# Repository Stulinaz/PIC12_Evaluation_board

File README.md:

# PIC12_Evaluation_board
kicad project of my custom PIC12 evaluation board

I'm Enrico and i am FCT board tester. I designed this board for rapid design of 8 pin microcontroller application that support my work.

The pic 12 board include:

-PICKIT connector on board.

-Large build area.

-Double Power supply from usb connector or from CR2032 battery for portable applications.

-Supports pullup and pulldown resistors for every pin.

-BOM is displayed on bottom silkscreen side.

TOP SIDE:

BOTTOM SIDE:

ASSEMBLED PCB:

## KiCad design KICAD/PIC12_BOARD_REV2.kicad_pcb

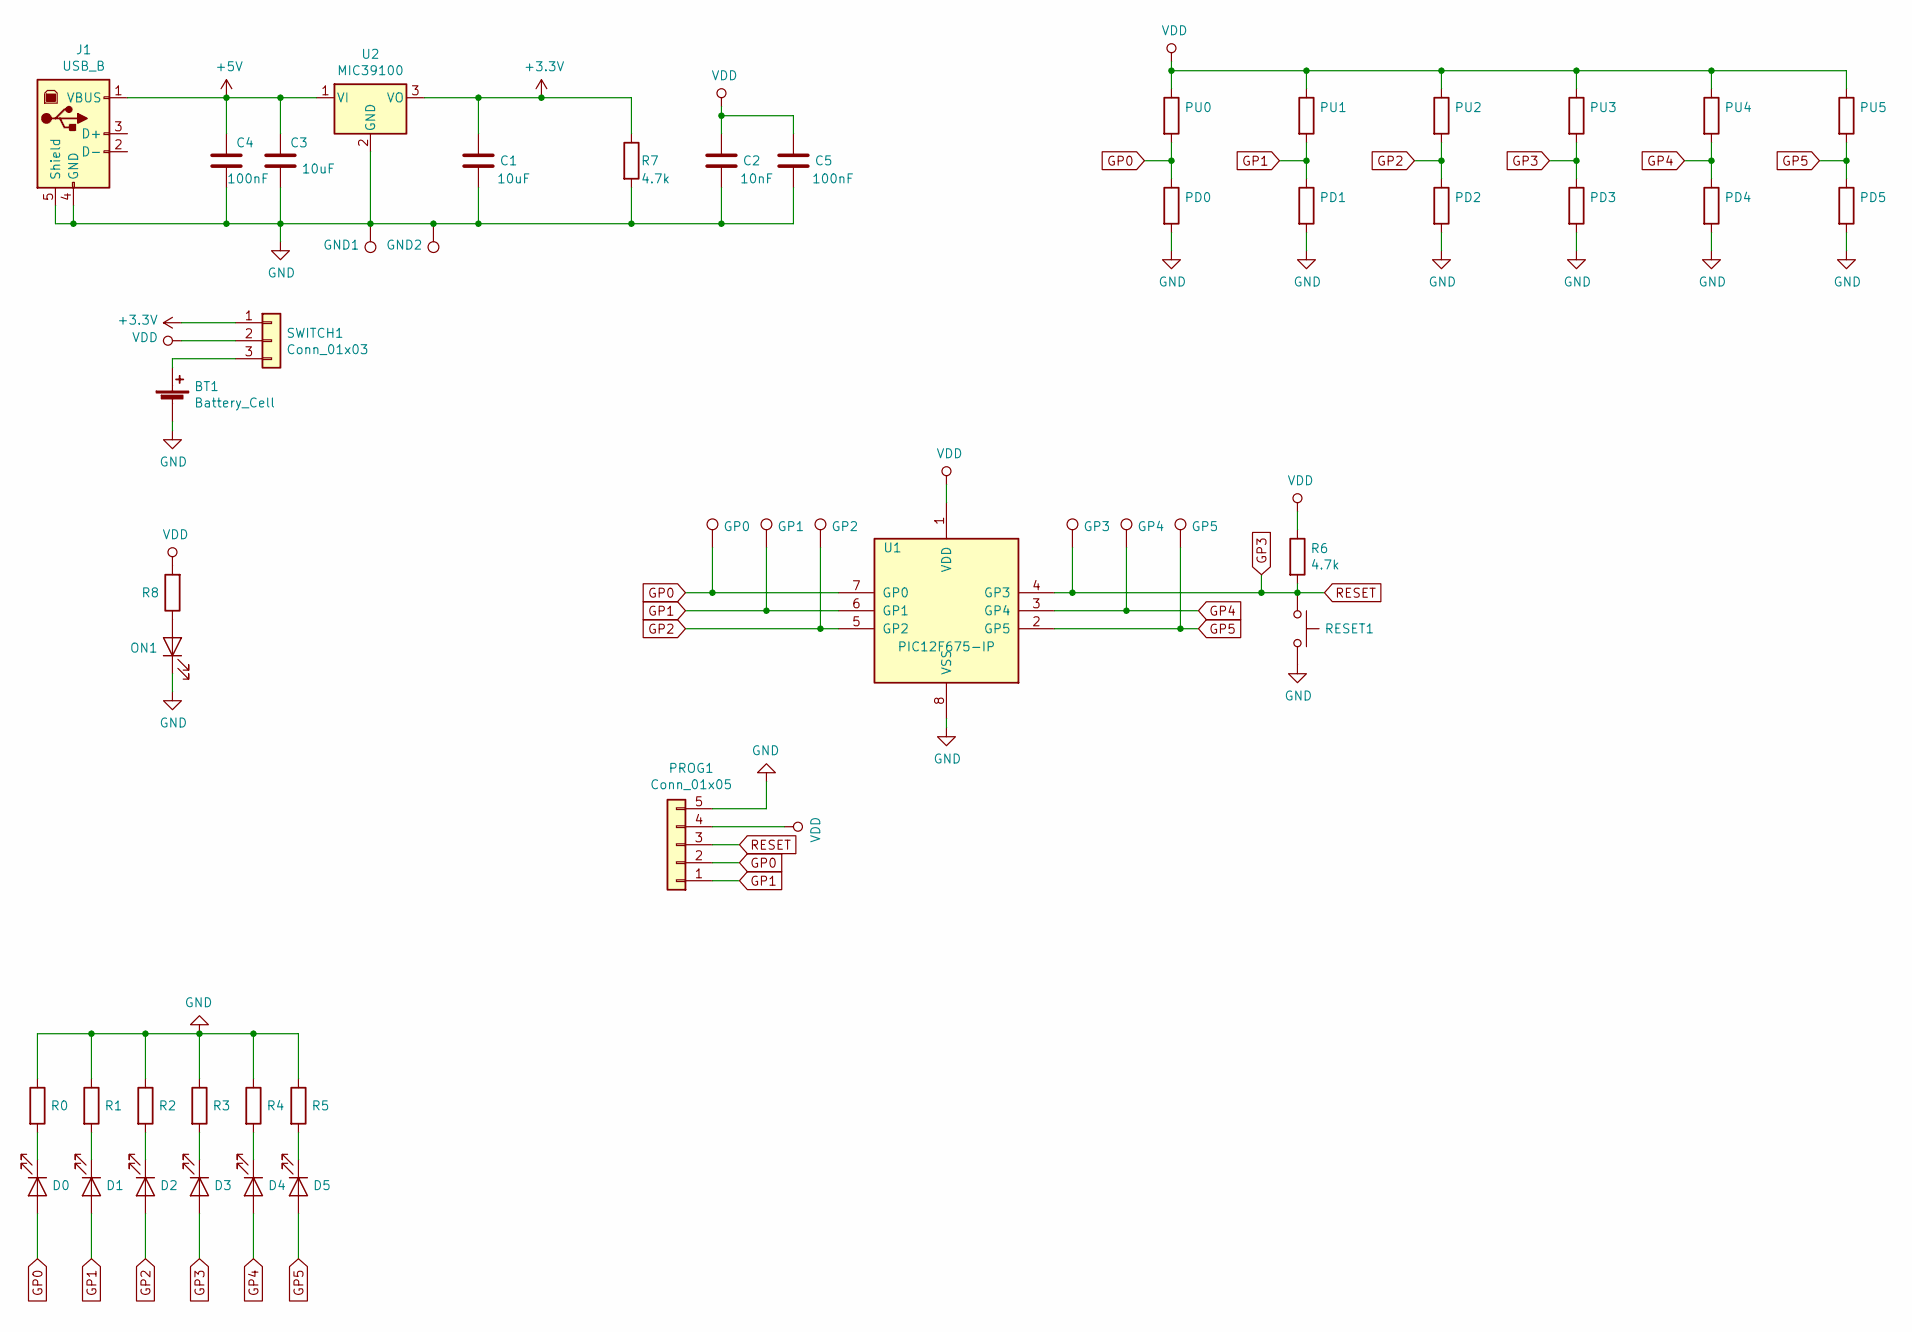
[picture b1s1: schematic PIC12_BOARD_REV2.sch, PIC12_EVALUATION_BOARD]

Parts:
BT1: Battery_Cell; BatteryHolder_Keystone_3034_1x20mm
C1, C3: 10uF; R_0805_2012Metric_Pad1.15x1.40mm_HandSolder
C2: 10nF; R_0805_2012Metric_Pad1.15x1.40mm_HandSolder
C4, C5: 100nF; R_0805_2012Metric_Pad1.15x1.40mm_HandSolder
D0, D1, D2, D3, D4, D5: LED; R_0805_2012Metric_Pad1.15x1.40mm_HandSolder
GND1, GND2: TestPoint; TP_EN0
GP0, GP1, GP2, GP3, GP4, GP5: TestPoint; TP_EN0
J1: USB_B; USB_Mini-B_Lumberg_2486_01_Horizontal
ON1: LED; R_0805_2012Metric_Pad1.15x1.40mm_HandSolder
PD0, PD1, PD2, PD3, PD4, PD5: 4.7k; R_0805_2012Metric_Pad1.15x1.40mm_HandSolder
PROG1: Conn_01x05; PinSocket_1x05_P2.54mm_Vertical
PU0, PU1, PU2, PU3, PU4, PU5: 4.7k; R_0805_2012Metric_Pad1.15x1.40mm_HandSolder
R0, R1, R2, R3, R4, R5: R; R_0805_2012Metric_Pad1.15x1.40mm_HandSolder
R6: 4.7k; R_0805_2012Metric
R7: 4.7k; R_0805_2012Metric_Pad1.15x1.40mm_HandSolder
R8: 220; R_0805_2012Metric_Pad1.15x1.40mm_HandSolder
RESET1: SW_Push; SW_PUSH_6mm
SWITCH1: Conn_01x03; PinHeader_1x03_P2.54mm_Vertical
U1: PIC12F675-IP; DIP-8_W7.62mm
U2: MIC39100; SOT-223-3_TabPin2

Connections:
+3V3: C1.1, R7.1, SWITCH1.1, U2.3 (VO)
+5V: C3.1, C4.1, J1.1 (VBUS), U2.1 (VI)
DATA+: J1.3 (D+)
DATA-: J1.2 (D-)
GND: BT1.2 (-), C1.2, C2.2, C3.2, C4.2, C5.2, GND1.1, GND2.1, J1.4 (GND), J1.5 (Shield), J1.6, ON1.1 (K), PD0.2, PD1.2, PD2.2, PD3.2, PD4.2, PD5.2, PROG1.5, R0.1, R1.1, R2.1, R3.1, R4.1, R5.1, R7.2, RESET1.2, U1.8 (VSS), U2.2 (GND)
GP0: D0.2 (A), GP0.1, PD0.1, PROG1.2, PU0.2, U1.7 (GP0)
GP1: D1.2 (A), GP1.1, PD1.1, PROG1.1, PU1.2, U1.6 (GP1)
GP2: D2.2 (A), GP2.1, PD2.1, PU2.2, U1.5 (GP2)
GP3: D3.2 (A), GP3.1, PD3.1, PROG1.3, PU3.2, R6.2, RESET1.1, U1.4 (GP3)
GP4: D4.2 (A), GP4.1, PD4.1, PU4.2, U1.3 (GP4)
GP5: D5.2 (A), GP5.1, PD5.1, PU5.2, U1.2 (GP5)
unnamed: BT1.1 (+), SWITCH1.3
unnamed: D0.1 (K), R0.2
unnamed: D1.1 (K), R1.2
unnamed: D2.1 (K), R2.2
unnamed: D3.1 (K), R3.2
unnamed: D4.1 (K), R4.2
unnamed: D5.1 (K), R5.2
unnamed: ON1.2 (A), R8.1
VDD: C2.1, C5.1, PROG1.4, PU0.1, PU1.1, PU2.1, PU3.1, PU4.1, PU5.1, R6.1, R8.2, SWITCH1.2, U1.1 (VDD); also elsewhere on the board

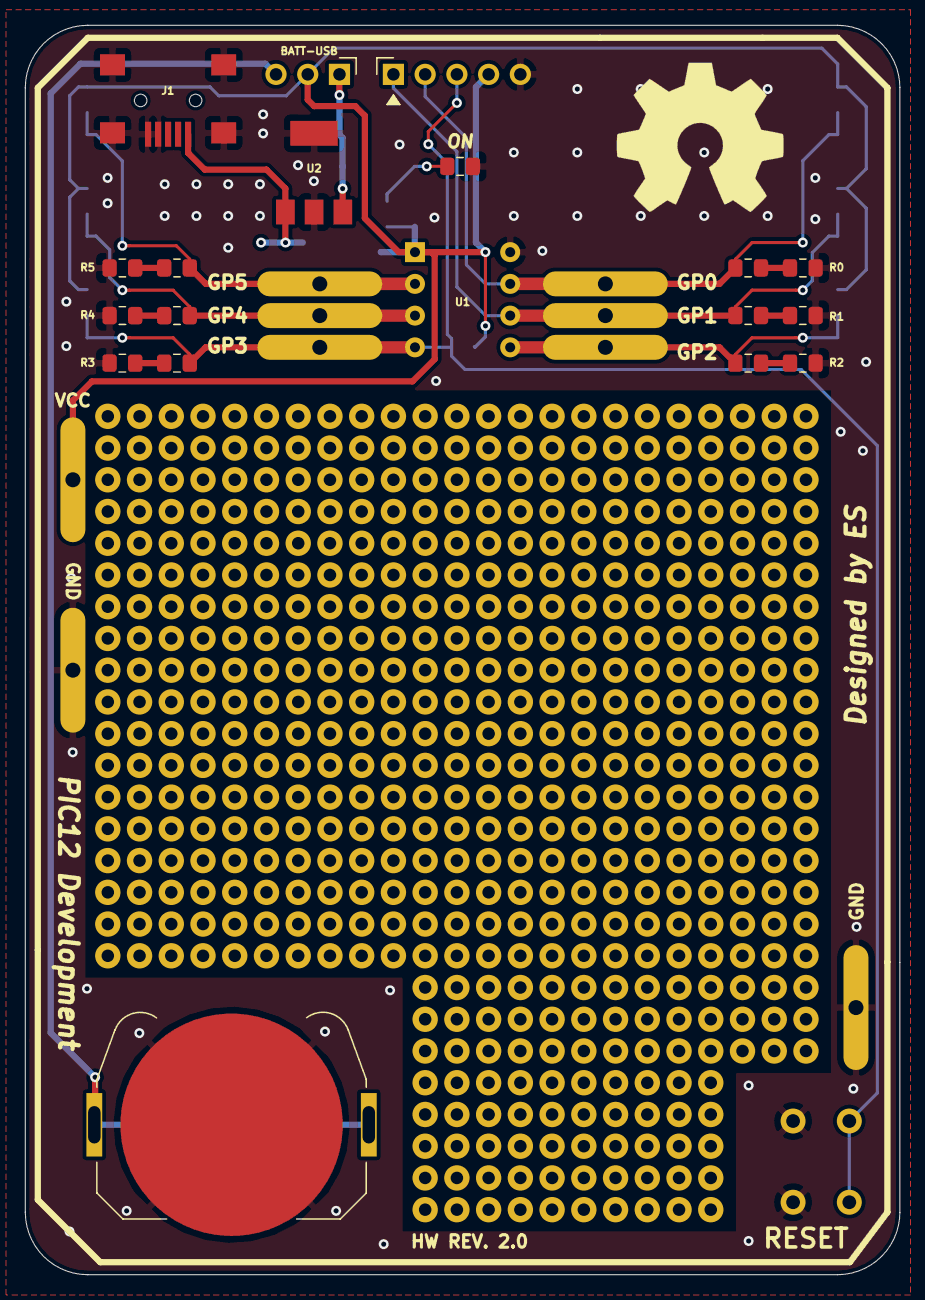
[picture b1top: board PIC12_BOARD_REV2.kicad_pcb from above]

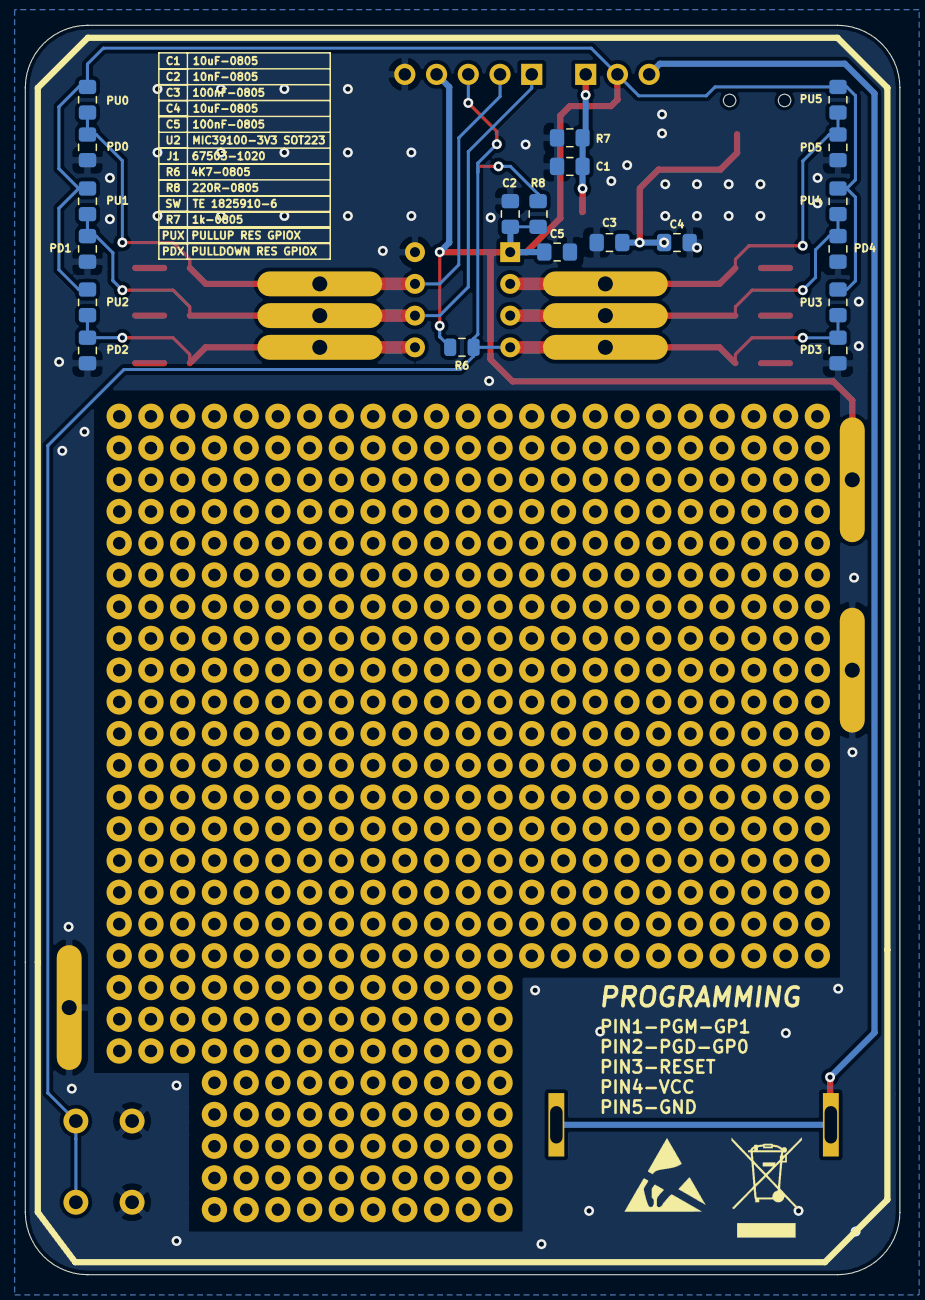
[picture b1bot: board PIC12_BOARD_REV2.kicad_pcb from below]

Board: 2 copper layers, 70.0 x 100.0 mm, 49 parts (20 on the bottom side), 18 nets.

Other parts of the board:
VCC1: TestPoint; TP_EN0

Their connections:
VDD: VCC1.1; also elsewhere on the board

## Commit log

2021-11-05 first_commit
2021-11-05 added_schematic
2021-11-05 open_source_logo
2021-11-25 added license file
2021-11-26 added bom and gerber files
